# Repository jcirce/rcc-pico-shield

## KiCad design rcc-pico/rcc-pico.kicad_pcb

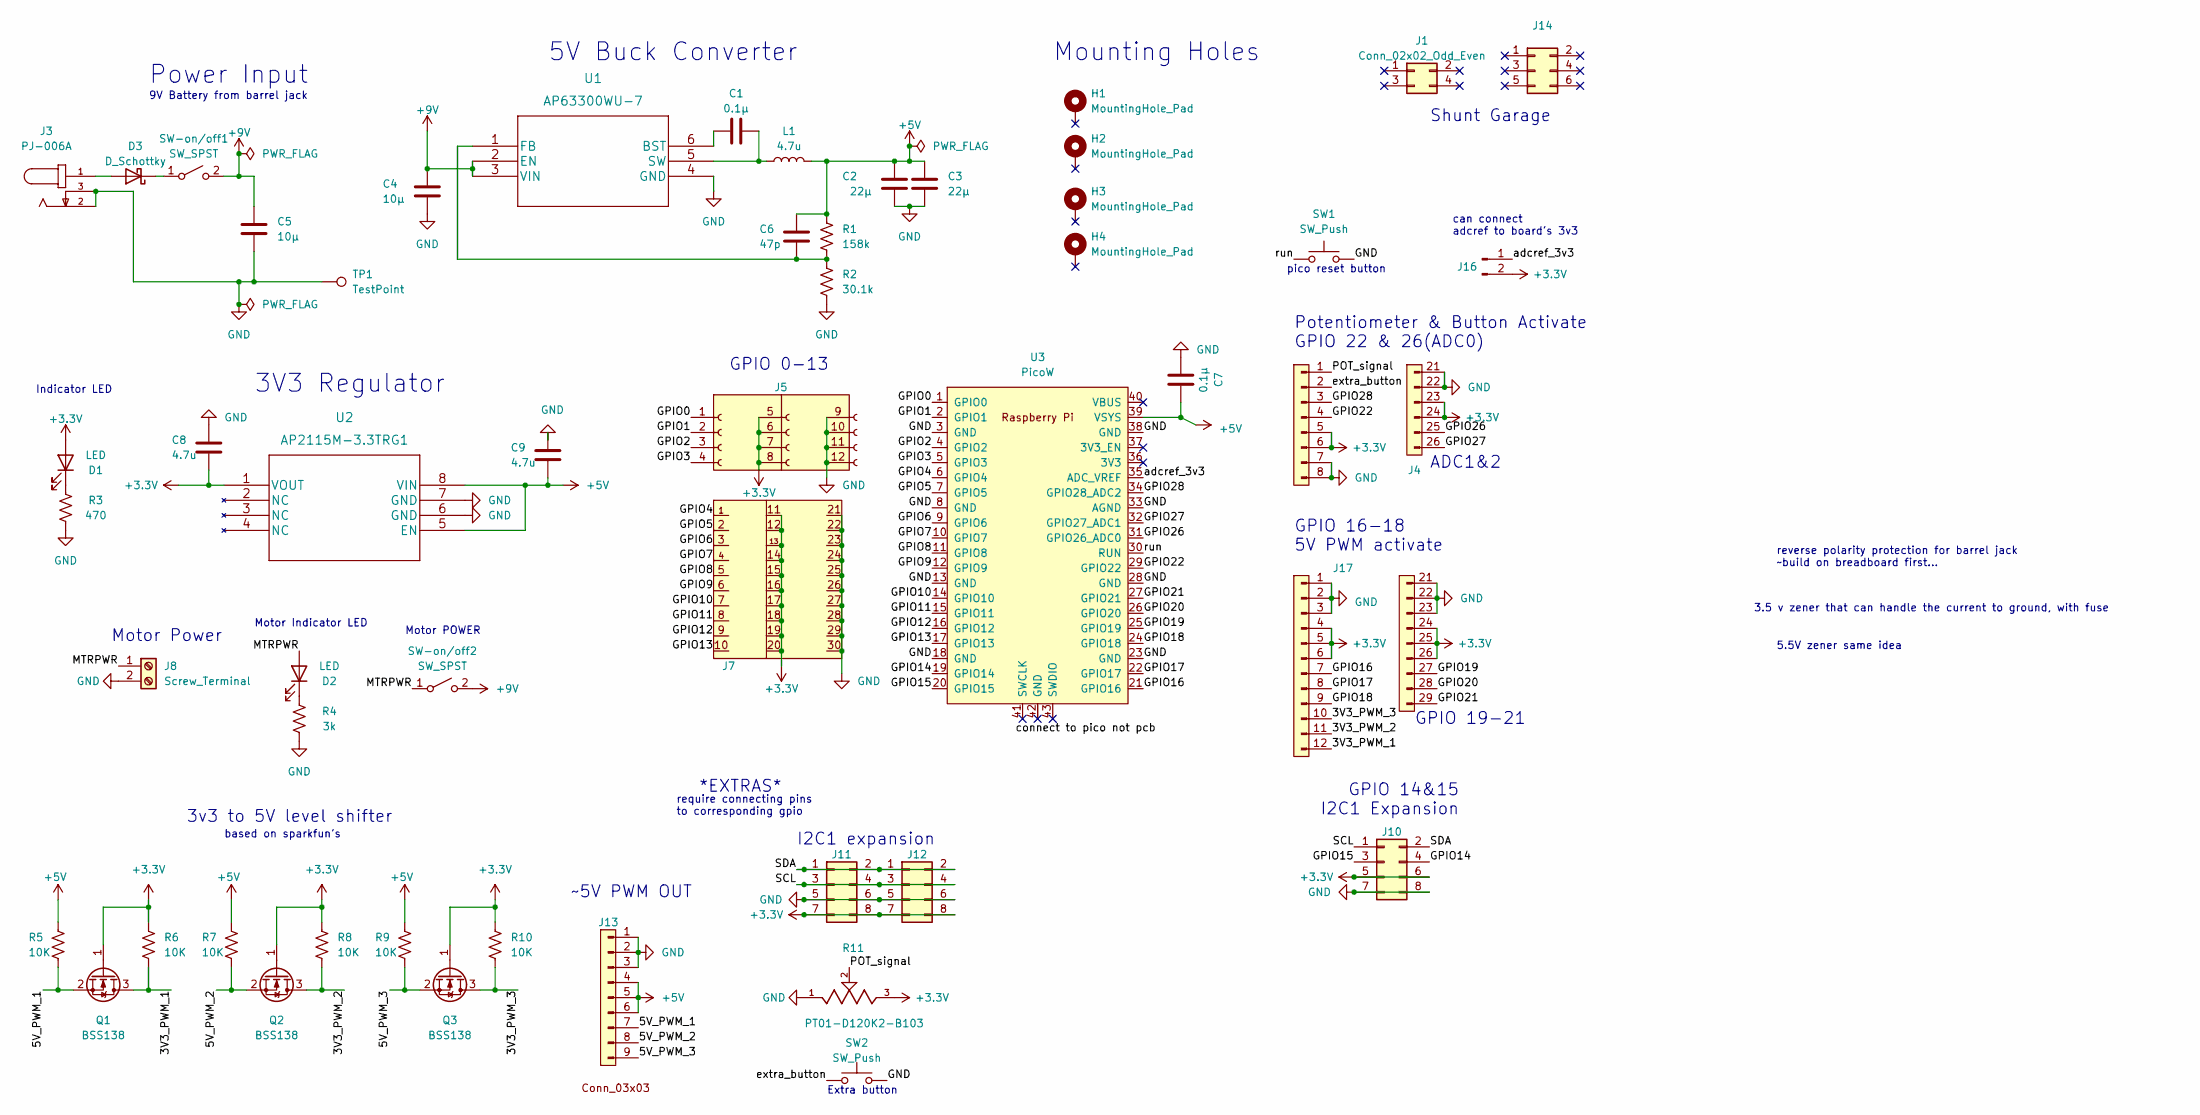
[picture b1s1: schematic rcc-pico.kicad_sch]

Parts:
C1, C7: 0.1μ; C_0402_1005Metric
C2, C3: 22μ; C_0805_2012Metric
C4, C5: 10μ; C_0805_2012Metric
C6: 47p; C_0603_1608Metric
C8, C9: 4.7u; C_0603_1608Metric
D1, D2: LED; LED_0603_1608Metric
D3: D_Schottky; DIOM5227X270N
H1, H2, H3, H4: MountingHole_Pad; MountingHole_3.2mm_M3_ISO7380_Pad
J1: Conn_02x02_Odd_Even; PinSocket_1x04_P2.54mm_Vertical
J3: PJ-006A; CUI_PJ-006A
J4: Conn_22,24-26
J5: Conn_3x4_female; PinHeader_3x04_P2.54mm_Vertical_gpio
J7: Conn_03x10; PinHeader_3x11_P2.54mm_Vertical
J8: Screw_Terminal; TCxx03_5mm_2x1
J10: Conn_02x04_Odd_Even; PinHeader_2x04_P2.54_Vertical_I2C_shunt
J11, J12: Conn_02x04_Odd_Even; PinHeader_2x04_P2.54_Vertical_I2C
J13: PinHeader_3x03_P2.54mm_Vertical_Servo
J14: Conn_02x05_Odd_Even; PinHeader_2x03_P2.54mm_Vertical
J16: Conn_01x02_Pin; PinHeader_1x02_P2.54mm_Vertical
J17: Conn_16-21
L1: 4.7u; BWVS00606045
Q1, Q2, Q3: BSS138; SOT-23
R1: 158k; R_0603_1608Metric
R2: 30.1k; R_0603_1608Metric
R3: 470; R_0603_1608Metric
R4: 3k; R_0603_1608Metric
R5, R6, R7, R8, R9, R10: 10K; R_0603_1608Metric
R11: PT01-D120K2-B103; TRIM_PT01-D120K2-B103; PARTREV 1.0
SW1, SW2: SW_Push; SW_TH_Tactile_Omron_B3F-10xx
SW-on/off1, SW-on/off2: SW_SPST; SW_OS102011MS2QN1
TP1: TestPoint; PinHeader_1x01_P2.54mm_Vertical
U1: AP63300WU-7; TSOT-23-6
U2: AP2115M-3.3TRG1
U3: PicoW; RPi_Pico_SMD_TH

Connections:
+3.3V: C8.1, D1.2 (A), J4.5, J4.6, J4.23 (Pin_3), J4.24 (Pin_4), J5.5, J5.6, J5.7, J5.8, J7.11, J7.12, J7.13, J7.14, J7.15, J7.16, J7.17, J7.18, J7.19, J7.20, J10.5, J10.6, J11.7, J11.8, J12.7, J12.8, J16.2, J17.4, J17.5, J17.6, J17.24 (Pin_4), J17.25 (5), J17.26 (6), Q1.1 (G), Q2.1 (G), Q3.1 (G), R6.1, R8.1, R10.1, R11.3, U2.1 (VOUT)
+5V: C2.1, C3.1, C6.2, C7.2, C9.1, J13.4, J13.5, J13.6, L1.2, R1.2, R5.1, R7.1, R9.1, U2.5 (EN), U2.8 (VIN), U3.39 (VSYS)
+9V: C4.1, C5.1, SW-on/off1.2 (B), SW-on/off2.2 (B), U1.2 (EN), U1.3 (VIN)
/3V3_PWM_1: J17.12, Q1.3 (D), R6.2
/3V3_PWM_2: J17.11, Q2.3 (D), R8.2
/3V3_PWM_3: J17.10, Q3.3 (D), R10.2
/5V_PWM_1: J13.7, Q1.2 (S), R5.2
/5V_PWM_2: J13.8, Q2.2 (S), R7.2
/5V_PWM_3: J13.9, Q3.2 (S), R9.2
/GPIO0: J5.1, U3.1 (GPIO0)
/GPIO1: J5.2, U3.2 (GPIO1)
/GPIO2: J5.3, U3.4 (GPIO2)
/GPIO3: J5.4, U3.5 (GPIO3)
/GPIO4: J7.1, U3.6 (GPIO4)
/GPIO5: J7.2, U3.7 (GPIO5)
/GPIO6: J7.3, U3.9 (GPIO6)
/GPIO7: J7.4, U3.10 (GPIO7)
/GPIO8: J7.5, U3.11 (GPIO8)
/GPIO9: J7.6, U3.12 (GPIO9)
/GPIO10: J7.7, U3.14 (GPIO10)
/GPIO11: J7.8, U3.15 (GPIO11)
/GPIO12: J7.9, U3.16 (GPIO12)
/GPIO13: J7.10, U3.17 (GPIO13)
/GPIO14: J10.4, U3.19 (GPIO14)
/GPIO15: J10.3, U3.20 (GPIO15)
/GPIO16: J17.7, U3.21 (GPIO16)
/GPIO17: J17.8, U3.22 (GPIO17)
/GPIO18: J17.9, U3.24 (GPIO18)
/GPIO19: J17.27 (7), U3.25 (GPIO19)
/GPIO20: J17.28 (8), U3.26 (GPIO20)
/GPIO21: J17.29 (9), U3.27 (GPIO21)
/GPIO22: J4.4, U3.29 (GPIO22)
/GPIO26: J4.25 (5), U3.31 (GPIO26_ADC0)
/GPIO27: J4.26 (6), U3.32 (GPIO27_ADC1)
/GPIO28: J4.3, U3.34 (GPIO28_ADC2)
/MTRPWR: D2.2 (A), J8.1, SW-on/off2.1 (A)
/POT_signal: J4.1, R11.2
/SCL: J10.1, J11.3, J11.4, J12.3, J12.4
/SDA: J10.2, J11.1, J11.2, J12.1, J12.2
/adcref_3v3: J16.1, U3.35 (ADC_VREF)
/extra_button: J4.2, SW2.1
/run: SW1.1, U3.30 (RUN)
GND: C2.2, C3.2, C4.2, C5.2, C7.1, C8.2, C9.2, J3.2, J3.3, J4.7, J4.8, J4.21 (Pin_1), J4.22 (Pin_2), J5.9, J5.10, J5.11, J5.12, J7.21, J7.22, J7.23, J7.24, J7.25, J7.26, J7.27, J7.28, J7.29, J7.30, J8.2, J10.7, J10.8, J11.5, J11.6, J12.5, J12.6, J13.1, J13.2, J13.3, J17.1, J17.2, J17.3, J17.21 (Pin_1), J17.22 (Pin_2), J17.23 (Pin_3), R2.2, R3.2, R4.2, R11.1, SW1.2, SW2.2, TP1.1, U1.4 (GND), U2.6 (GND), U2.7 (GND), U3.3 (GND), U3.8 (GND), U3.13 (GND), U3.18 (GND), U3.23 (GND), U3.28 (GND), U3.33 (AGND), U3.38 (GND)
unnamed: D1.1 (K), R3.1
unnamed: D2.1 (K), R4.1
unnamed: D3.2 (A), J3.1
unnamed: D3.1 (K), SW-on/off1.1 (A)
unnamed: C1.1, U1.6 (BST)
unnamed: C6.1, R1.1, R2.1, U1.1 (FB)
unnamed: C1.2, L1.1, U1.5 (SW)

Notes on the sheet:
require connecting pins to corresponding gpio
5.5V zener same idea
Mounting Holes
GPIO 16-18 5V PWM activate
GPIO 19-21
I2C1 expansion
reverse polarity protection for barrel jack ~build on breadboard first...
3V3 Regulator
3v3 to 5V level shifter
can connect adcref to board's 3v3
~5V PWM OUT
Extra button
Potentiometer & Button Activate GPIO 22 & 26(ADC0)
Power Input
based on sparkfun's
pico reset button
Motor Power
5V Buck Converter
ADC1&2
9V Battery from barrel jack
3.5 v zener that can handle the current to ground, with fuse
Shunt Garage
GPIO 0-13
Indicator LED
Motor Indicator LED
Motor POWER
*EXTRAS*
GPIO 14&15 I2C1 Expansion

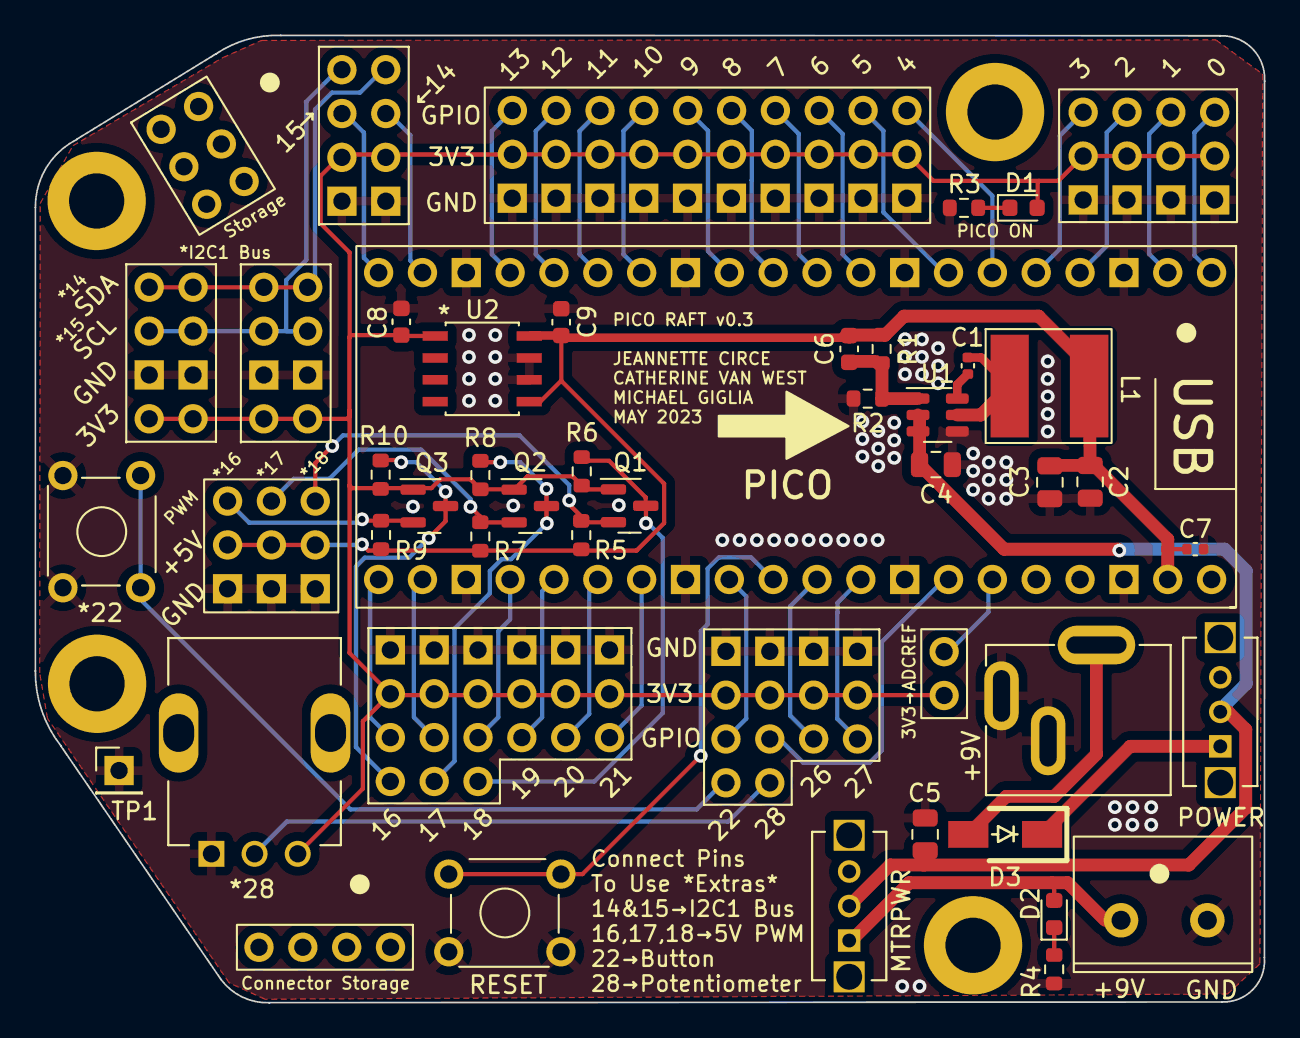
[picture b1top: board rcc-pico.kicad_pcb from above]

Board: 2 copper layers, 71.2 x 56.0 mm, 52 parts (0 on the bottom side), 50 nets.

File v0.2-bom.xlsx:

Source: | /Users/jeannettecirce/Desktop/rcc-pico-shield/rcc-pico/rcc-pico.kicad_sch
Date: | 2023 April 18, Tuesday 10:33:05
Tool: | Eeschema 7.0.1-0
Generator: | /Volumes/KiCad/KiCad/KiCad.app/Contents/SharedSupport/plugins/bom_csv_grouped_b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
Component Count: | 51
Collated Components:
Item | Qty | Reference(s) | Value | LibPart | Footprint | Datasheet | DNP | MANUFACTURER | MAXIMUM_PACKAGE_HEIGHT | PARTREV | STANDARD
1 | 2 | C1, C7 | 0.1μ | Device:C | Capacitor_SMD:C_0603_1608Metric | ~ |  |  |  |  |  | 1276-1043-1-ND
2 | 2 | C2, C3 | 22μ | Device:C | Capacitor_SMD:C_0805_2012Metric | ~ |  |  |  |  |  | 1276-1202-1-ND
3 | 2 | C4, C5 | 10μ | Device:C | Capacitor_SMD:C_0805_2012Metric | ~ |  |  |  |  |  | 1276-1096-1-ND
4 | 1 | C6 | 47p | Device:C | Capacitor_SMD:C_0603_1608Metric | ~ |  |  |  |  |  | 1292-1528-1-ND
5 | 2 | C8, C9 | 4.7u | Device:C | Capacitor_SMD:C_0603_1608Metric | ~ |  |  |  |  |  | 1276-1045-1-ND
6 | 2 | D1, D2 | LED | Device:LED | LED_SMD:LED_0603_1608Metric | ~ |  |  |  |  |  | 3147-B1911USD-20D000114U1930CT-ND
9 | 1 | J3 | PJ-006A | power:PJ-006A | PicoShieldHeaders:CUI_PJ-006A |  |  | CUI INC |  |  | Manufacturer recommendations | CP-006A-ND
13 | 1 | J8 | Screw_Terminal | Connector:Screw_Terminal_01x02 | PicoShieldHeaders:TCxx03_5mm_2x1 | ~ |  |  |  |  |  | TC0203620000G-ND
20 | 1 | L1 | 4.7u | Device:L | PicoShieldHeaders:BWVS00606045 | ~ |  |  |  |  |  | 553-BWVS006060454R7ML1CT-ND
21 | 3 | Q1, Q2, Q3 | BSS138 | Transistor_FET:BSS138 | Package_TO_SOT_SMD:SOT-23 | https://www.onsemi.com/pub/Collateral/BSS138-D.PDF |  |  |  |  |  | 4530-BSS138CT-ND
22 | 1 | R1 | 158k | Device:R_US | Resistor_SMD:R_0603_1608Metric | ~ |  |  |  |  |  | 311-158KHRCT-ND
23 | 1 | R2 | 30.1k | Device:R_US | Resistor_SMD:R_0603_1608Metric | ~ |  |  |  |  |  | 13-RC0603FR-1330K1LCT-ND
24 | 1 | R3 | 470 | Device:R_US | Resistor_SMD:R_0603_1608Metric | ~ |  |  |  |  |  | 1292-WR06X471JTLCT-ND
25 | 1 | R4 | 3k | Device:R_US | Resistor_SMD:R_0603_1608Metric | ~ |  |  |  |  |  | 1292-WR06X332JTLCT-ND
26 | 6 | R5, R6, R7, R8, R9, R10 | 10K | Device:R_US | Resistor_SMD:R_0603_1608Metric | ~ |  |  |  |  |  | 1292-WR06X103JTLCT-ND
27 | 1 | R11 | PT01-D120K2-B103 | Pico_Shield_Headers:PT01-D120K2-B103 | Potentiometer:TRIM_PT01-D120K2-B103 |  |  | CUI Devices | 26.8 mm | 1 | Manufacturer Recommendations | 2223-PT01-D120K2-B103-ND
28 | 2 | SW1, SW2 | SW_Push | Switch:SW_Push | Button_Switch_THT:SW_TH_Tactile_Omron_B3F-10xx | ~ |  |  |  |  |  | SW402-ND
29 | 2 | SW-on/off1, SW-on/off2 | SW_SPST | Switch:SW_SPST | PicoShieldHeaders:SW_OS102011MS2QN1 | ~ |  |  |  |  |  | CKN9565-ND
31 | 1 | U1 | AP63300WU-7 | ultralibrarian:AP63300WU-7 | Package_TO_SOT_SMD:TSOT-23-6 |  |  |  |  |  |  | 31-AP63300WU-7CT-ND
32 | 1 | U2 | AP2115M-3.3TRG1 | Regulator_Linear:AP2115M-3.3TRG1 | PicoShieldHeaders:AP2115M-3.3TRG1 |  |  |  |  |  |  | AP2115M-3.3TRG1DICT-ND
 |  |  |  |  | Shunts |  |  |  |  |  |  | 1849-09200-71-BDGB00-ND
NOT DIGIKEY
30 | 1 | TP1 | TestPoint | Connector:TestPoint | Connector_PinHeader_2.54mm:PinHeader_1x01_P2.54mm_Vertical | ~
33 | 1 | U3 | PicoW | RPi_Pico:PicoW | PicoShieldHeaders:RPi_Pico_SMD_TH
14 | 1 | J10 | Conn_02x04_Odd_Even | Connector_Generic:Conn_02x04_Odd_Even | PicoShieldHeaders:PinHeader_2x04_P2.54_Vertical_I2C_shunt | ~
15 | 2 | J11, J12 | Conn_02x04_Odd_Even | Connector_Generic:Conn_02x04_Odd_Even | PicoShieldHeaders:PinHeader_2x04_P2.54_Vertical_I2C | ~
16 | 1 | J13 | ~ | Pico_Shield_Headers:Conn_03x03 | PicoShieldHeaders:PinHeader_3x03_P2.54mm_Vertical_Servo
17 | 1 | J14 | Conn_02x05_Odd_Even | Connector_Generic:Conn_02x03_Odd_Even | Connector_PinHeader_2.54mm:PinHeader_2x03_P2.54mm_Vertical | ~
18 | 1 | J16 | Conn_01x02_Pin | Connector:Conn_01x02_Pin | Connector_PinHeader_2.54mm:PinHeader_1x02_P2.54mm_Vertical | ~
19 | 1 | J17 | ~ | Pico_Shield_Headers:Conn_16-21 | PicoShieldHeaders:Conn_16-21
8 | 1 | J1 | Conn_02x02_Odd_Even | Connector_Generic:Conn_02x02_Odd_Even | Connector_PinSocket_2.54mm:PinSocket_1x04_P2.54mm_Vertical | ~
7 | 4 | H1, H2, H3, H4 | MountingHole_Pad | Mechanical:MountingHole_Pad | MountingHole:MountingHole_3.2mm_M3_ISO7380_Pad | ~
10 | 1 | J4 | ~ | Pico_Shield_Headers:Conn_22,24-26 | PicoShieldHeaders:Conn_22,24-26
11 | 1 | J5 | Conn_3x4_female | Connector:Conn_3x4_female | PicoShieldHeaders:PinHeader_3x04_P2.54mm_Vertical_gpio
12 | 1 | J7 | Conn_03x10 | Connector:Conn_03x10 | PicoShieldHeaders:PinHeader_3x11_P2.54mm_Vertical

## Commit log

2023-03-29 first version of rcc-pico shield pcb
2023-03-31 new schematic with LDO
2023-04-01 finished schematic
2023-04-03 finished schematic and layout
2023-04-03 first layout of traces
2023-04-03 ordered JLC
2023-04-03 adding BOM
2023-04-15 new schematic
2023-04-15 new layout and screenprint
2023-04-18 finished traces for v0.2
2023-04-18 finished DRC, added fiducals and name, cleaned up schematic a bit, still needs some work
2023-04-18 fixed D2 footprint
2023-04-18 final touches, fixed footprints
2023-04-18 changed 0.1uH footprint, added v0.2 BOM
2023-04-18 ordering v0.2
2023-05-04 v0.3 modifications, added input protection diode
2023-05-05 v0.3 for ordering, cleaned up screenprint and rearranged 9v cap to be next to the diode for ease
2023-05-05 new bill of materials with orders for 50 boards based on what we have in stock already
2023-05-05 updated bom

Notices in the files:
parts and their libraries:
Copyright 2021 Accelerated Designs. All rights reserved.
